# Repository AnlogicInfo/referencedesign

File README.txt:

Reference Design for Anlogic PLD devices.

Copyright 2011-2017 Anlogic Technologies.

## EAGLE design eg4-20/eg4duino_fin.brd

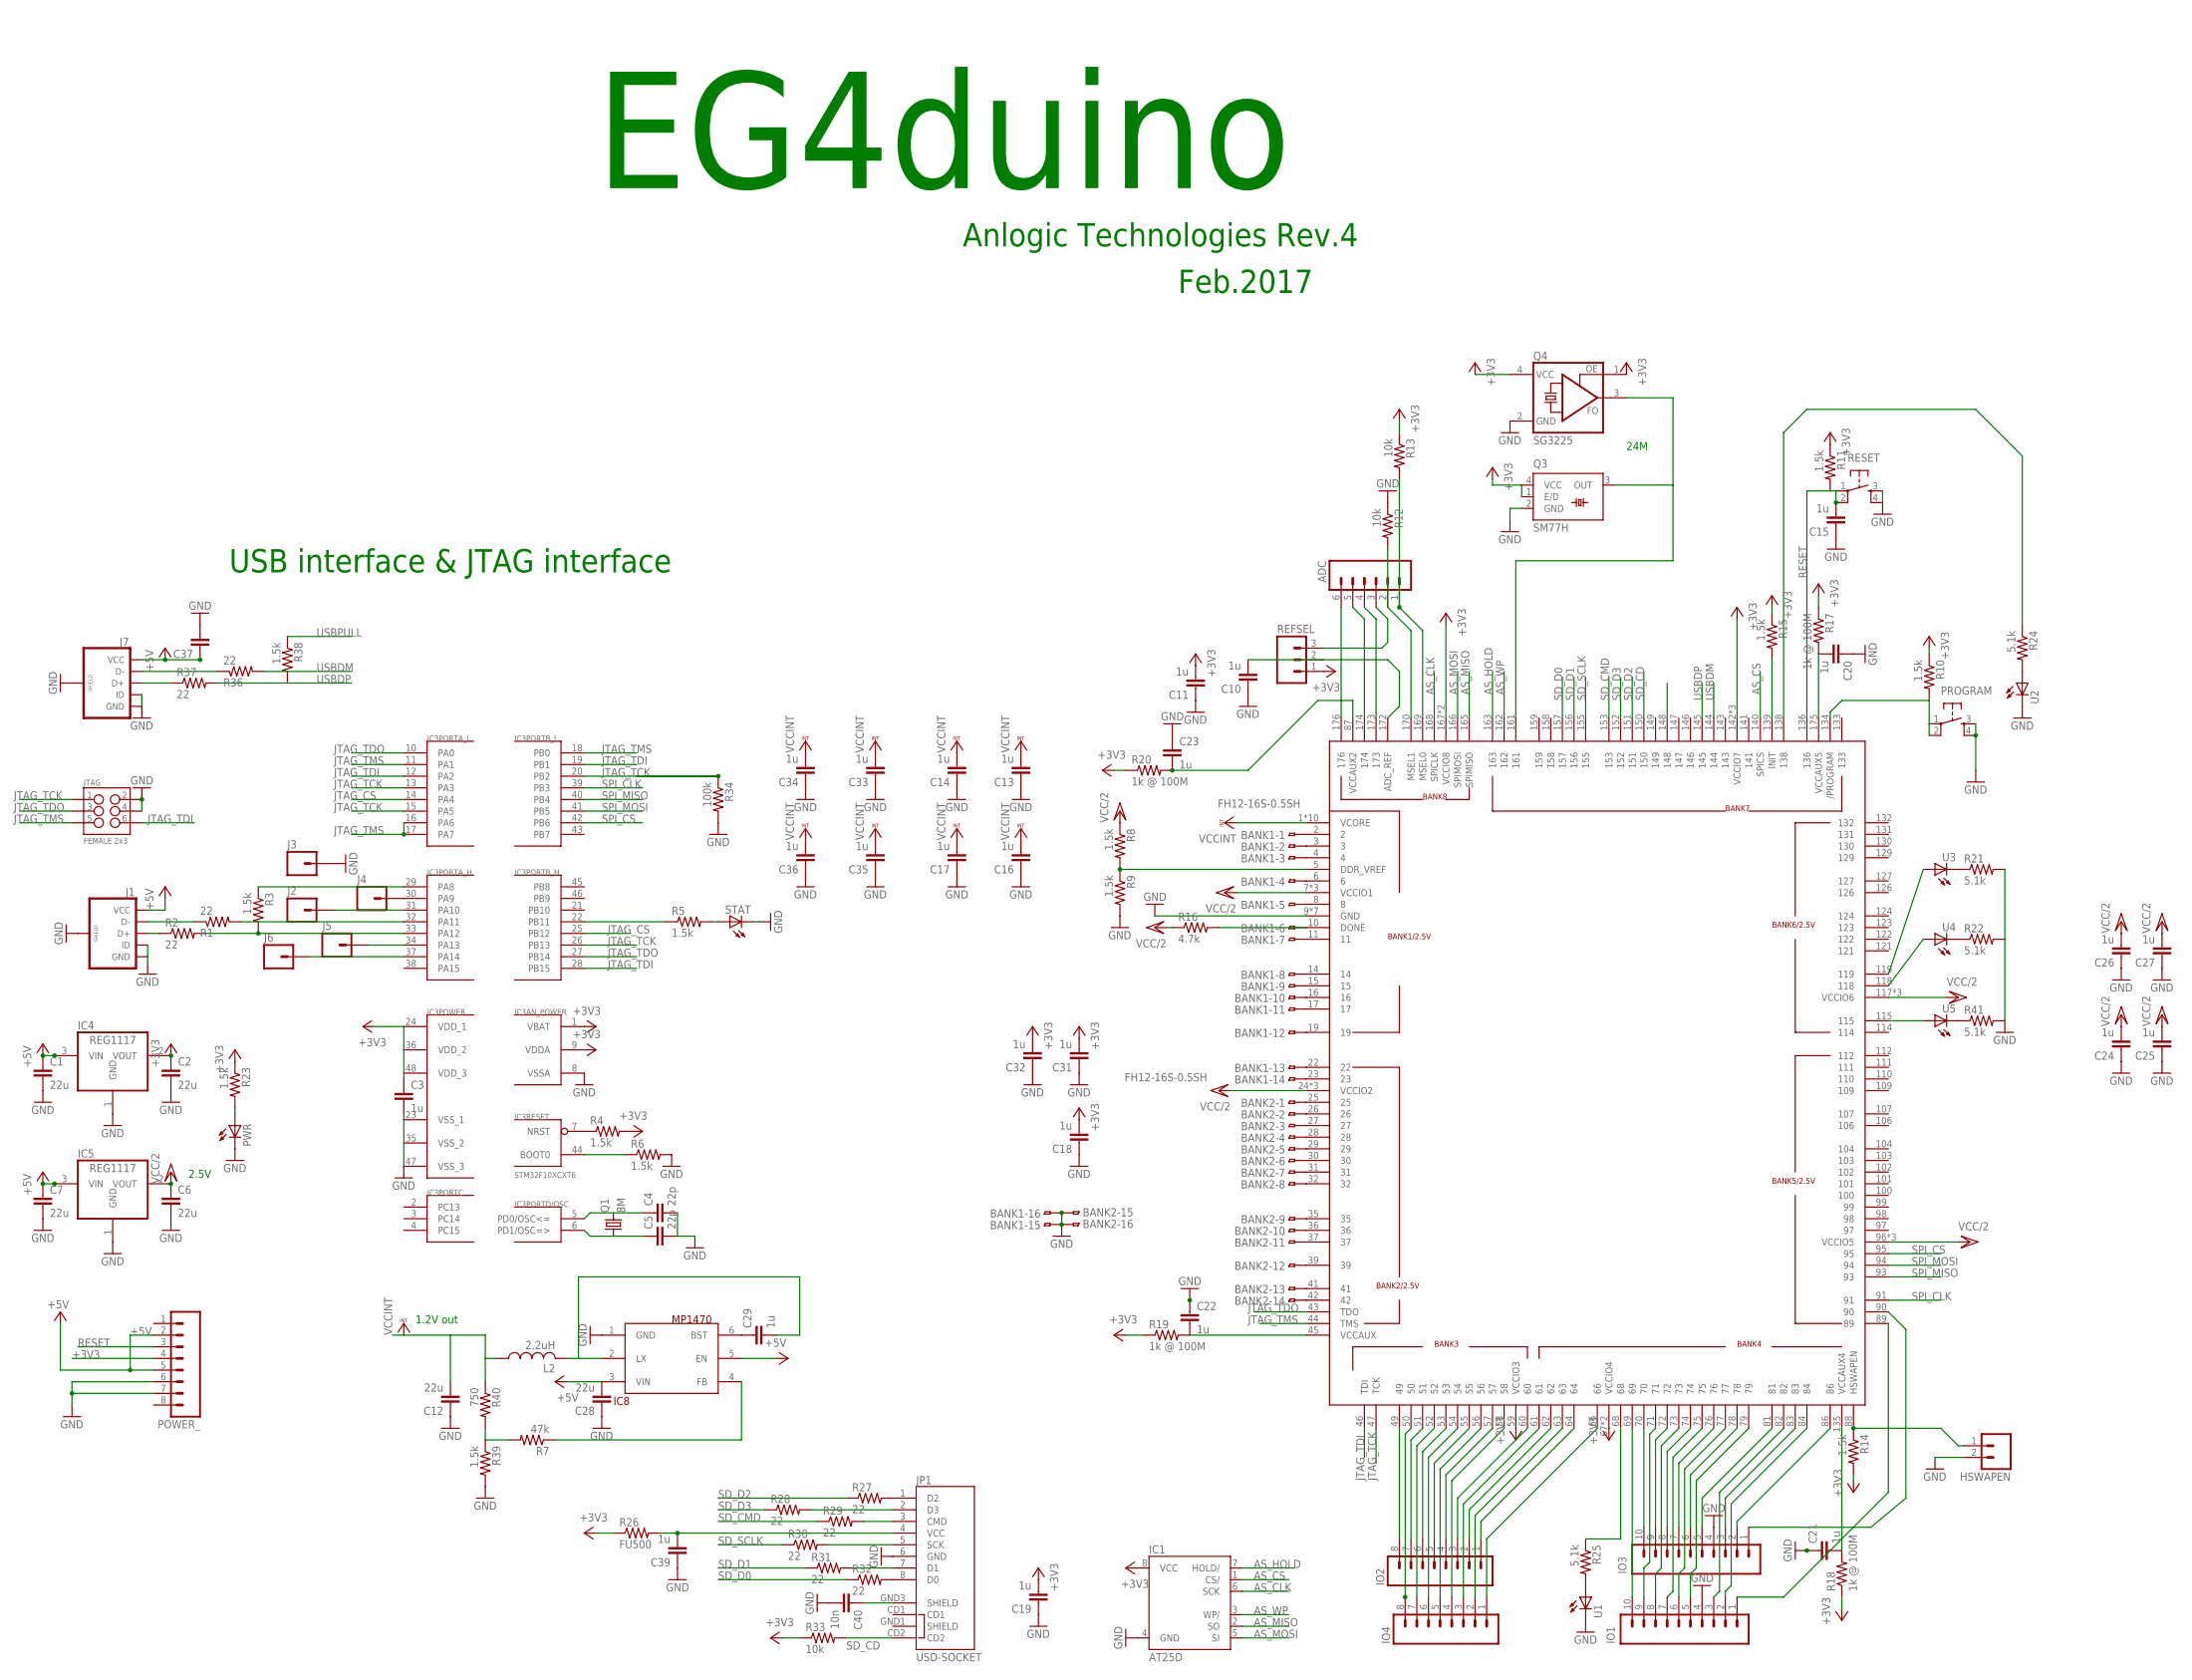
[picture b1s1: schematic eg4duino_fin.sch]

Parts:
ADC: M06SILK_FEMALE_PTH; 1X06
BANK1, BANK2: FH12-16S-0.5SH
C1, C2, C6, C7, C12, C28: 22u; C0805
C3, C10, C11, C13, C14, C15, C16, C17, C18, C19, C20, C21, C22, C23, C24, C25, C26, C27, C29, C31, C32, C33, C34, C35, C36, C39: 1u; C0805
C4, C5: 22p; C0805
C37: C-EUC0805; C0805
C40: 10n; C0805
HSWAPEN: M02PTH; 1X02
IC1: AT25D; SOIC8
IC2: EG4D20EG176; ELQFP176L
IC3: STM32F10XCXT6; TQFP48
IC4, IC5: REG1117; SOT223
IC8: MP1470; SOT23-6L
IO1, IO3: M10SILK_FEMALE_PTH; 1X10
IO2, IO4: M08SILK_FEMALE_PTH; 1X08
J1, J7: USB_MICROB_PLUGCONN-11752; USB-B-MICRO-SMD_V03
J2, J3, J4, J5, J6: M01; 0805SMD
JP1: USD-SOCKET; MICROSD_1:1
JTAG: FEMALE 2x3; 2X3
L2: 2.2uH; L4532P
POWER_: M08SILK_FEMALE_PTH; 1X08
PROGRAM: 10-XXSMD; B3F-10SMD
PWR: LEDCHIP-LED0805; CHIP-LED0805
Q1: 8M; HC49/S
Q3: SM77H
Q4: SG3225; 3225
R1, R2: 22; M0805
R3, R4, R5, R6, R23: 1.5k; M0805
R7: 47k; R0805
R8, R9, R11, R14, R15, R39: 1.5k; R0805
R10, R38: 1.5k; R0603
R12, R13, R33: 10k; R0805
R16: 4.7k; R0603
R17, R18, R19, R20: 1k @ 100M; R0805
R21, R22, R24, R25, R41: 5.1k; M0805
R26: FU500; R0805
R27, R28, R29, R30, R31, R32: 22; R0201
R34: 100k; R0603
R36, R37: 22; R0603W
R40: 750; R0805
REFSEL: M03PTH; 1X03
RESET: 10-XXSMD; B3F-10SMD
STAT: LEDCHIP-LED0805; CHIP-LED0805
U1, U2, U3, U4, U5: LEDCHIP-LED0805; CHIP-LED0805

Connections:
+3V3: C2.1, C3.1, C11.2, C18.2, C19.2, C31.2, C32.2, IC1.8 (VCC), IC2.59 (VCCIO3), IC2.67 (VCCIO4), IC2.80 (VCCIO4), IC2.142 (VCCIO7), IC2.154 (VCCIO7), IC2.160 (VCCIO7), IC2.167 (VCCIO8), IC2.171 (VCCIO8), IC3.1 (VBAT), IC3.9 (VDDA), IC3.24 (VDD_1), IC3.36 (VDD_2), IC3.48 (VDD_3), IC4.2 (VOUT), POWER_.4, Q3.1 (E/D), Q3.4 (VCC), Q4.1 (OE), Q4.4 (VCC), R4.2, R10.1, R11.1, R13.1, R14.2, R15.1, R17.1, R18.1, R19.1, R20.1, R23.1, R26.1, R33.1, REFSEL.1
+5V: C1.1, C7.1, C28.2, C37.1, IC4.3 (VIN), IC5.3 (VIN), IC8.3 (VIN), IC8.5 (EN), J1.VBUS (VCC), J7.VBUS (VCC), POWER_.2, POWER_.5
AS_CLK: IC1.6 (SCK), IC2.168 (SPICLK)
AS_CS: IC1.1 (CS/), IC2.140 (SPICS)
AS_HOLD: IC1.7 (HOLD/), IC2.163
AS_MISO: IC1.2 (SO), IC2.165 (SPIMISO)
AS_MOSI: IC1.5 (SI), IC2.166 (SPIMOSI)
AS_WP: IC1.3 (WP/), IC2.162
GND: BANK1.15, BANK1.16, BANK2.15, BANK2.16, C1.2, C2.2, C3.2, C4.2, C5.2, C6.2, C7.2, C10.1, C11.1, C12.1, C13.1, C14.1, C15.1, C16.1, C17.1, C18.1, C19.1, C20.1, C21.1, C22.1, C23.1, C24.1, C25.1, C26.1, C27.1, C28.1, C31.1, C32.1, C33.1, C34.1, C35.1, C36.1, C37.2, C39.1, C40.2, HSWAPEN.2, IC1.4 (GND), IC2.9 (GND), IC2.13 (GND), IC2.21 (GND), IC2.33 (GND), IC2.38 (GND), IC2.116 (GND), IC2.EGND (GND), IC3.8 (VSSA), IC3.23 (VSS_1), IC3.35 (VSS_2), IC3.47 (VSS_3), IC4.1 (GND), IC5.1 (GND), IC8.1 (GND), IO1.4, IO3.4, J1.GND, J1.ID, J1.SHIELD1 (SHIELD), J1.SHIELD2 (SHIELD), J1.SHIELD3 (SHIELD), J3.1, J7.GND, J7.ID, J7.SHIELD1 (SHIELD), J7.SHIELD2 (SHIELD), J7.SHIELD3 (SHIELD), JP1.6 (GND), JTAG.2, JTAG.4, POWER_.6, POWER_.7, PROGRAM.3 (S), PROGRAM.4 (S1), PWR.C, Q3.2 (GND), Q4.2 (GND), R6.2, R9.2, R12.1, R21.2, R22.2, R34.2, R39.2, R41.2, RESET.3 (S), RESET.4 (S1), STAT.C, U1.C, U2.C
JTAG_CS: IC3.14 (PA4), IC3.25 (PB12)
JTAG_TCK: IC2.47 (TCK), IC3.13 (PA3), IC3.15 (PA5), IC3.20 (PB2), IC3.26 (PB13), JTAG.1, R34.1
JTAG_TDI: IC2.46 (TDI), IC3.12 (PA2), IC3.19 (PB1), IC3.28 (PB15), JTAG.6
JTAG_TDO: IC2.43 (TDO), IC3.10 (PA0), IC3.27 (PB14), JTAG.3
JTAG_TMS: IC2.44 (TMS), IC3.11 (PA1), IC3.16 (PA6), IC3.17 (PA7), IC3.18 (PB0), JTAG.5
unnamed: ADC.6, IC2.176
unnamed: ADC.5, IC2.174
unnamed: ADC.4, IC2.173
unnamed: ADC.3, REFSEL.3
unnamed: ADC.2, IC2.170 (MSEL1), R12.2
unnamed: ADC.1, IC2.169 (MSEL0), R13.2
unnamed: IC2.69, IO1.10
unnamed: IC2.70, IO3.10
unnamed: IC2.71, IO1.9
unnamed: IC2.72, IO3.9
unnamed: IC2.73, IO1.8
unnamed: IC2.74, IO3.8
unnamed: IC2.75, IO1.7
unnamed: IC2.76, IO3.7
unnamed: IC2.77, IO1.6
unnamed: IC2.78, IO3.6
unnamed: IC2.79, IO1.5
unnamed: IC2.83, IO3.3
unnamed: IC2.81, IO3.5
unnamed: IC2.82, IO1.3
unnamed: IC2.84, IO1.2
unnamed: IC2.86, IO3.2
unnamed: IC2.89, IO1.1
unnamed: IC2.90, IO3.1
unnamed: J1.D+, R2.1
unnamed: J1.D-, R1.1
unnamed: IC3.32 (PA11), R1.2
unnamed: IC3.33 (PA12), R2.2, R3.2
unnamed: IC3.29 (PA8), R3.1
unnamed: IC3.31 (PA10), J2.1
unnamed: IC3.30 (PA9), J4.1
unnamed: IC3.7 (NRST), R4.1
unnamed: IC3.22 (PB11), R5.1
unnamed: R5.2, STAT.A
unnamed: C4.1, IC3.5 (PD0/OSC<=), Q1.2
unnamed: C5.1, IC3.6 (PD1/OSC=>), Q1.1
unnamed: IC3.44 (BOOT0), R6.1
unnamed: IC2.49, IO2.8
unnamed: IC2.51, IO2.7
unnamed: IC2.53, IO2.6
unnamed: IC2.54, IO4.6
unnamed: IC2.55, IO2.5
unnamed: IC2.56, IO4.5
unnamed: IC2.57, IO2.4
unnamed: IC2.58, IO4.4
unnamed: IC2.60, IO2.3
unnamed: IC2.61, IO4.3
unnamed: IC2.62, IO2.2
unnamed: IC2.63, IO4.2
unnamed: IC2.64, IO2.1
unnamed: IC2.66, IO4.1
unnamed: IC2.161, Q3.3 (OUT), Q4.3 (FO)
unnamed: C10.2, IC2.172 (ADC_REF), REFSEL.2
unnamed: IC2.119, U3.A
unnamed: IC2.118, U4.A
unnamed: C29.2, IC8.2 (LX), L2.2
unnamed: C29.1, IC8.6 (BST)
unnamed: IC8.4 (FB), R7.1
unnamed: R7.2, R39.1, R40.2
unnamed: IC2.5 (DDR_VREF), R8.2, R9.1
unnamed: BANK1.1, IC2.2
unnamed: BANK1.2, IC2.3
unnamed: BANK1.3, IC2.4
unnamed: BANK1.4, IC2.6
unnamed: BANK1.5, IC2.8
unnamed: IC3.34 (PA13), J5.1
unnamed: BANK1.7, IC2.11
unnamed: BANK1.8, IC2.14
unnamed: BANK1.9, IC2.15
unnamed: BANK1.10, IC2.16
unnamed: BANK1.11, IC2.17
unnamed: BANK1.12, IC2.19
unnamed: BANK1.13, IC2.22
unnamed: BANK1.14, IC2.23
unnamed: BANK2.1, IC2.25
unnamed: BANK2.2, IC2.26
unnamed: BANK2.3, IC2.27
unnamed: BANK2.4, IC2.28
unnamed: BANK2.5, IC2.29
unnamed: BANK2.6, IC2.30
unnamed: BANK2.7, IC2.31
unnamed: BANK2.8, IC2.32
unnamed: BANK2.9, IC2.35
unnamed: BANK2.10, IC2.36
unnamed: BANK2.11, IC2.37
unnamed: BANK2.12, IC2.39
unnamed: BANK2.13, IC2.41
unnamed: BANK2.14, IC2.42
unnamed: C20.2, IC2.175 (VCCAUX5), R17.2
unnamed: HSWAPEN.1, IC2.88 (HSWAPEN), R14.1
unnamed: IC2.139 (INIT), R15.2
unnamed: C21.2, IC2.135 (VCCAUX4), R18.2
unnamed: C22.2, IC2.45 (VCCAUX), R19.2
unnamed: C23.2, IC2.87 (VCCAUX2), R20.2
unnamed: IC2.115, U5.A
unnamed: PWR.A, R23.2
unnamed: R24.2, U2.A
unnamed: IC2.138, R24.1
unnamed: R25.2, U1.A
unnamed: IC2.68, R25.1
unnamed: C39.2, JP1.4 (VCC), R26.2
unnamed: JP1.1 (D2), R27.2
unnamed: IC2.134 (/PROGRAM), PROGRAM.1, PROGRAM.2 (P1), R10.2
unnamed: JP1.2 (D3), R28.2
unnamed: JP1.3 (CMD), R29.2
unnamed: JP1.8 (D0), R32.2
unnamed: JP1.7 (D1), R31.2
unnamed: IC3.37 (PA14), J6.1
unnamed: JP1.5 (SCK), R30.2
unnamed: C40.1, JP1.GND3 (SHIELD)
unnamed: BANK1.6, IC2.10 (DONE), R16.2
unnamed: J7.D-, R36.1
unnamed: J7.D+, R37.1
unnamed: R21.1, U3.C
unnamed: R22.1, U4.C
unnamed: R41.1, U5.C
RESET: C15.2, IC2.136, POWER_.3, R11.2, RESET.1, RESET.2 (P1)
SD_CD: IC2.150, JP1.CD2, R33.2
SD_CMD: IC2.153, R29.1
SD_D0: IC2.157, R32.1
SD_D1: IC2.156, R31.1
SD_D2: IC2.151, R27.1
SD_D3: IC2.152, R28.1
SD_SCLK: IC2.155, R30.1
SPI_CLK: IC2.91, IC3.39 (PB3)
SPI_CS: IC2.95, IC3.42 (PB6)
SPI_MISO: IC2.93, IC3.40 (PB4)
SPI_MOSI: IC2.94, IC3.41 (PB5)
USBDM: IC2.144, R36.2
USBDP: IC2.145, R37.2, R38.2
USBPULL: IC2.148, R38.1
USER_RX: IC2.52, IO4.7
USER_TX: IC2.50, IO4.8
VCC/2: C6.1, C24.2, C25.2, C26.2, C27.2, IC2.7 (VCCIO1), IC2.12 (VCCIO1), IC2.18 (VCCIO1), IC2.24 (VCCIO2), IC2.34 (VCCIO2), IC2.40 (VCCIO2), IC2.96 (VCCIO5), IC2.105 (VCCIO5), IC2.108 (VCCIO5), IC2.117 (VCCIO6), IC2.120 (VCCIO6), IC2.125 (VCCIO6), IC5.2 (VOUT), R8.1, R16.1
VCCINT: C12.2, C13.2, C14.2, C16.2, C17.2, C33.2, C34.2, C35.2, C36.2, IC2.1 (VCORE), IC2.20 (VCORE), IC2.48 (VCORE), IC2.65 (VCORE), IC2.85 (VCORE), IC2.92 (VCORE), IC2.113 (VCORE), IC2.128 (VCORE), IC2.137 (VCORE), IC2.164 (VCORE), L2.1, R40.1

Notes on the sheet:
1.2V out
2.5V
EG4duino
Anlogic Technologies Rev.4
Feb.2017
USB interface & JTAG interface
24M

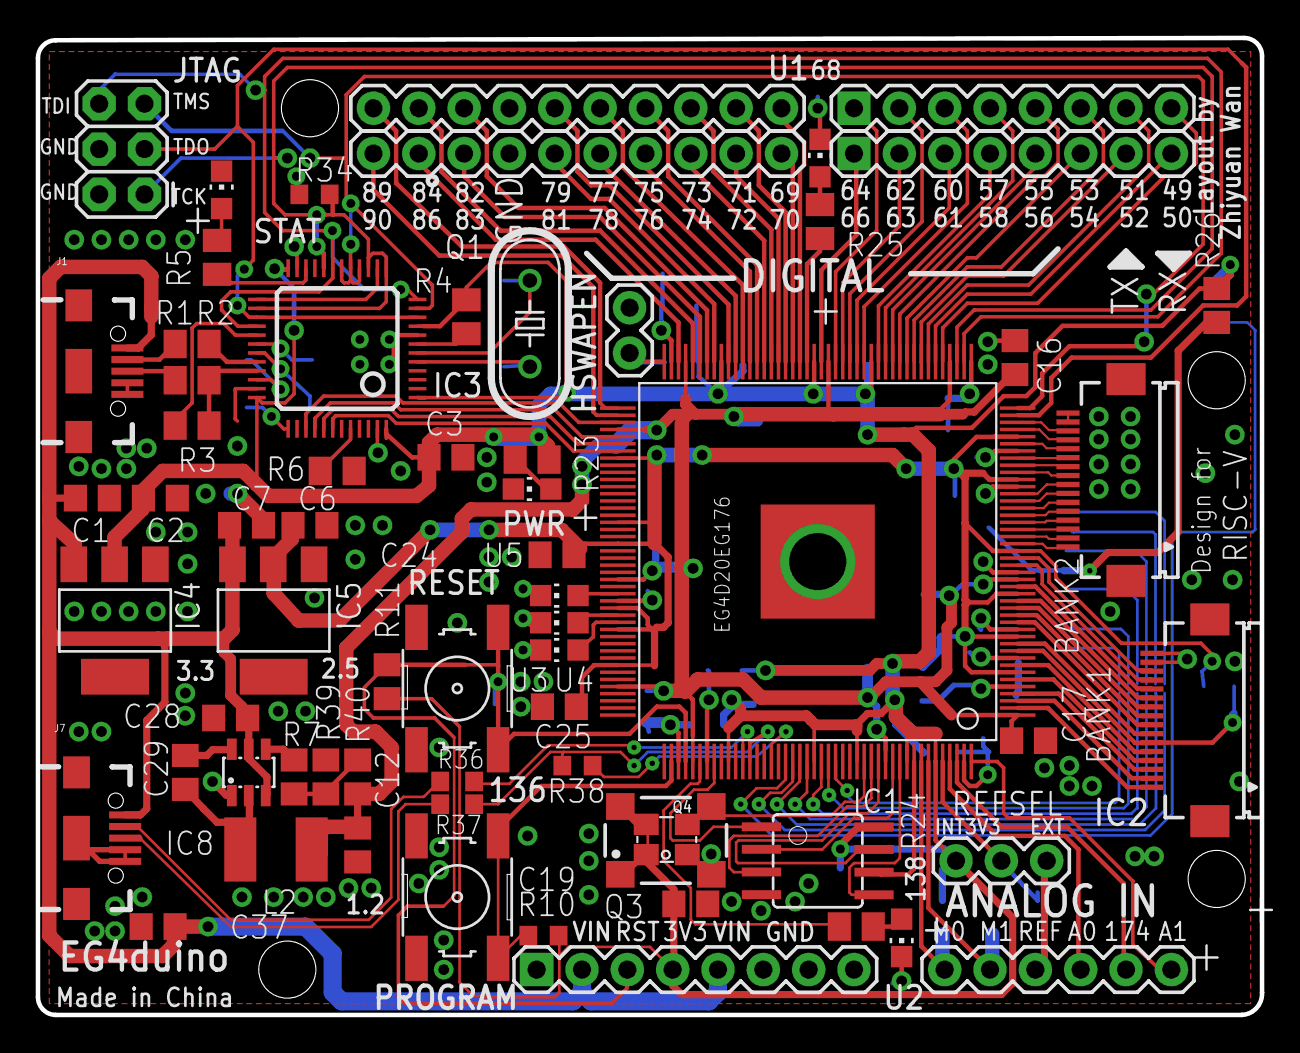
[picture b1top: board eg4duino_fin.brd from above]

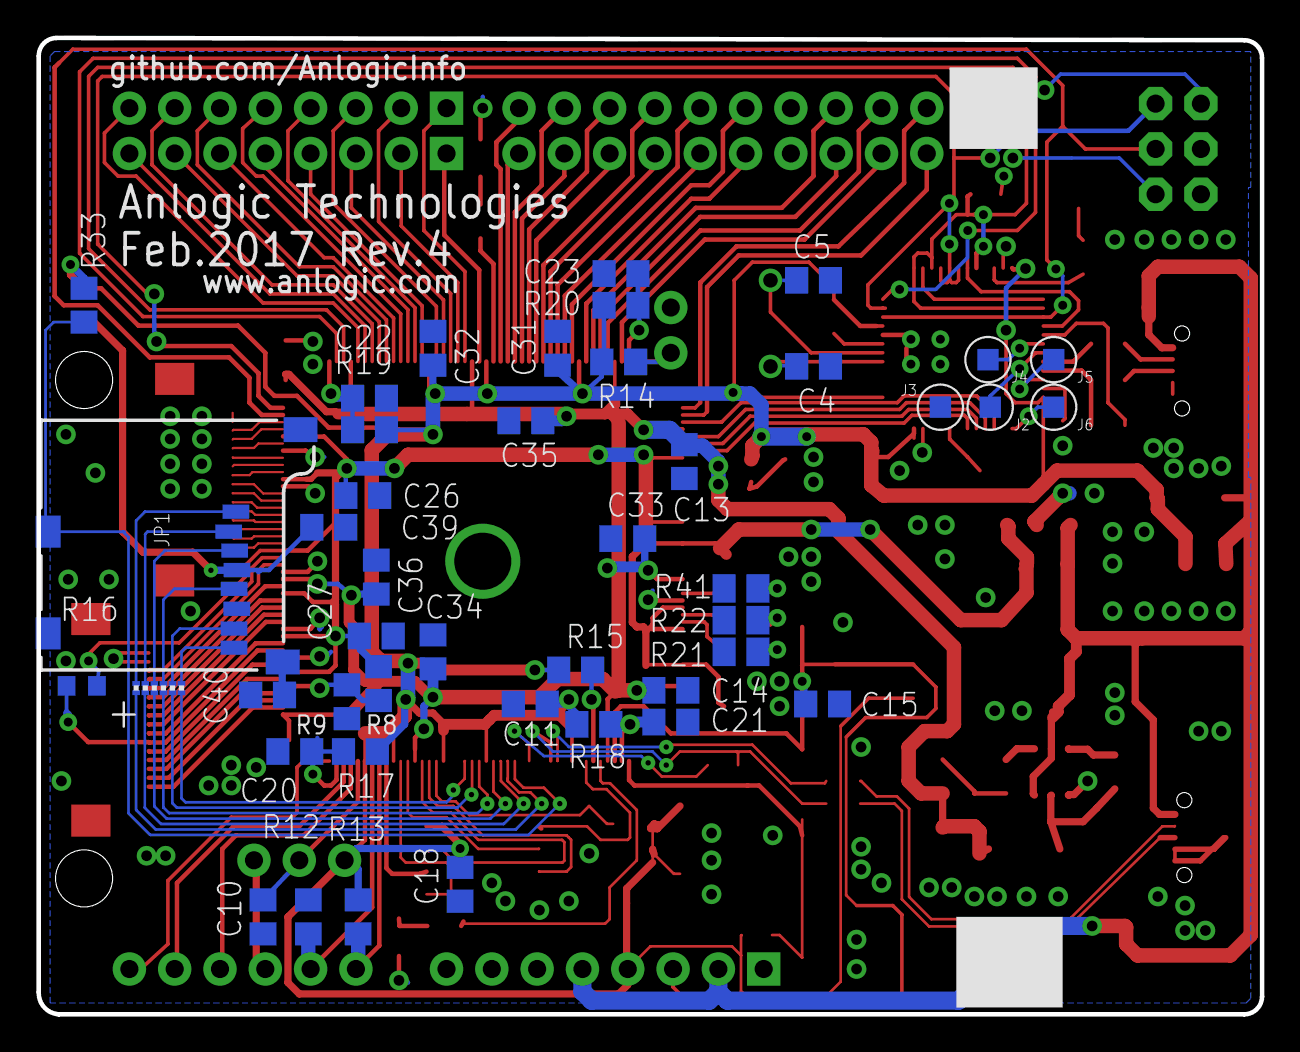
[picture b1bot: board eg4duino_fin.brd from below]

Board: 2 copper layers, 68.6 x 54.7 mm, 114 parts (49 on the bottom side), 149 nets.

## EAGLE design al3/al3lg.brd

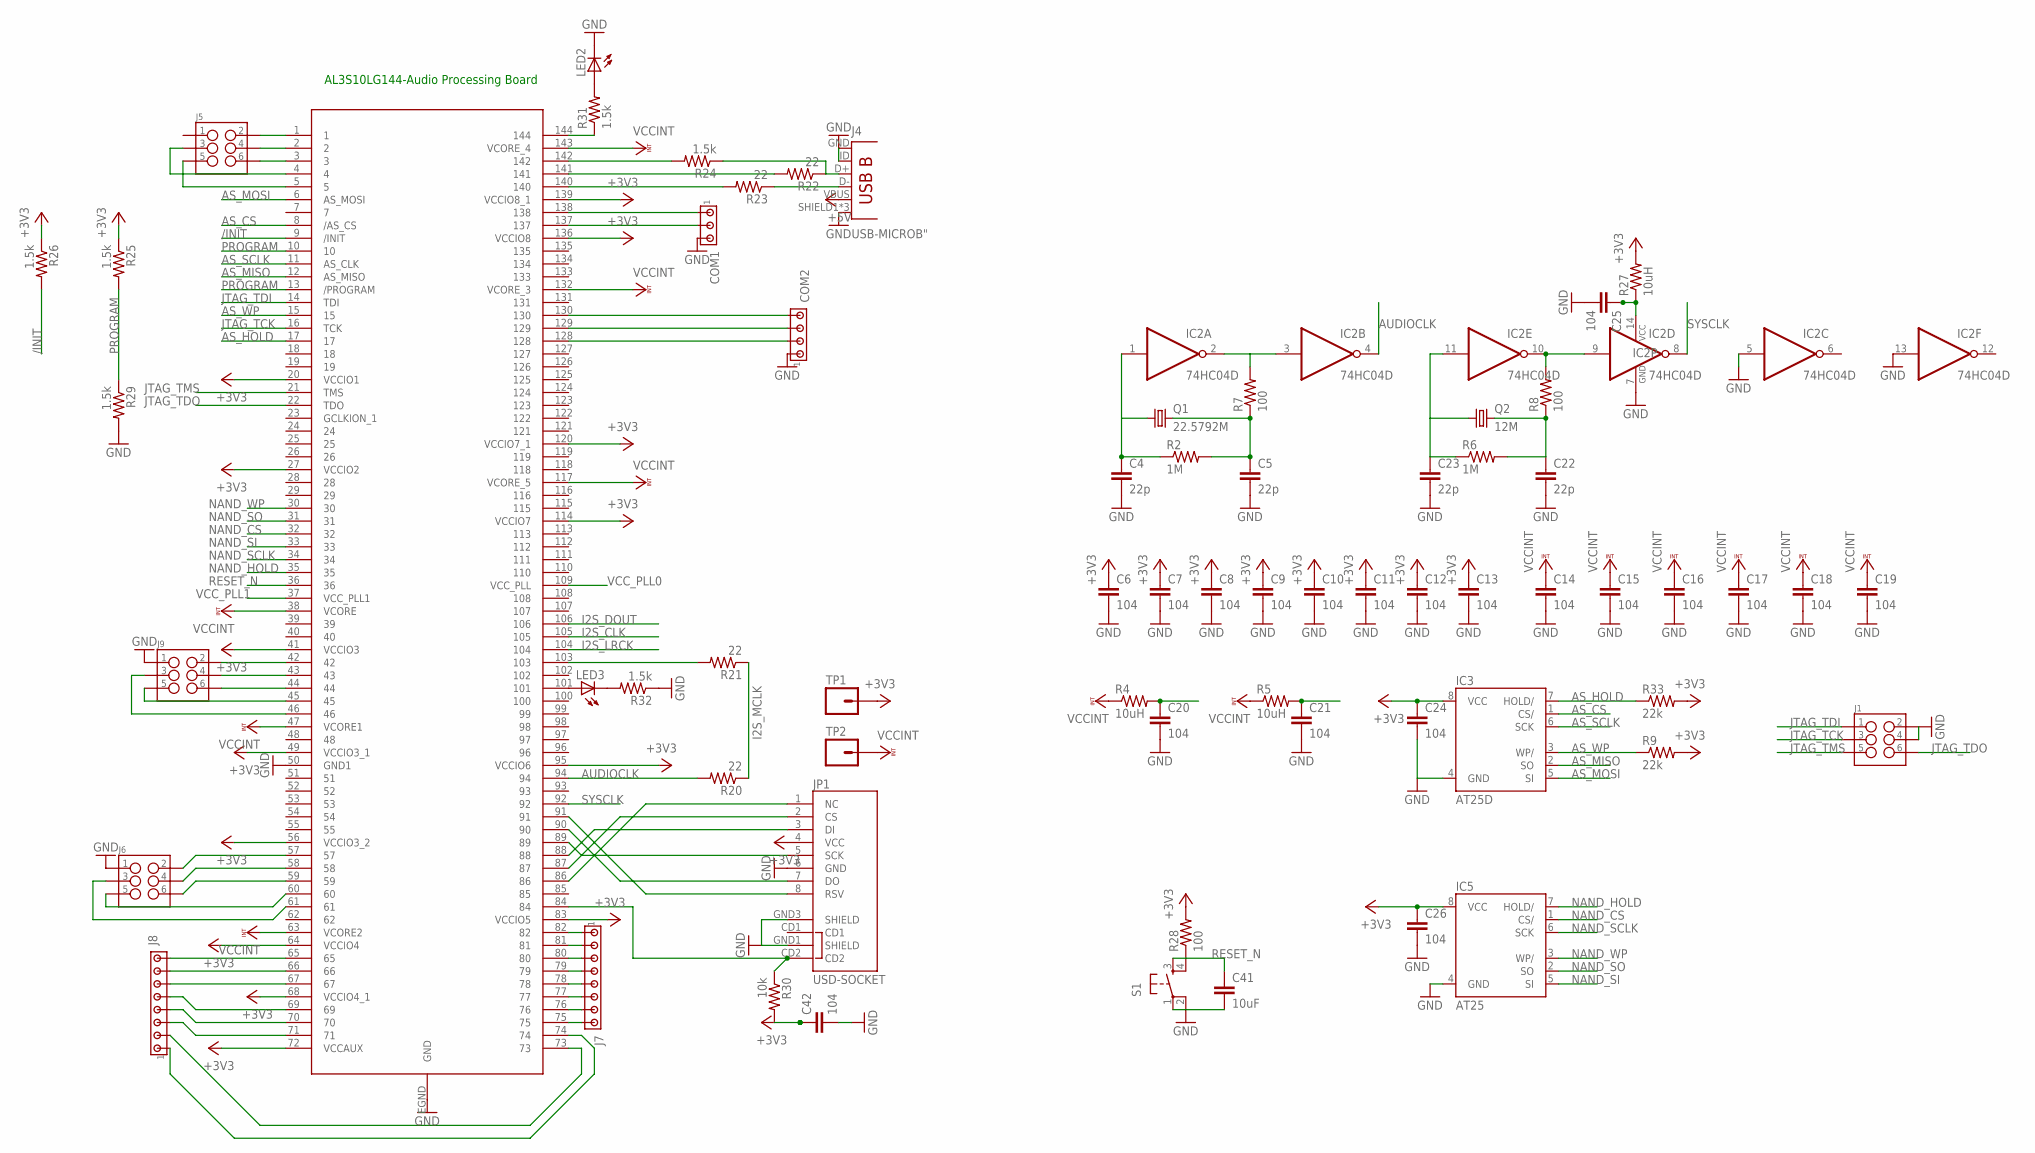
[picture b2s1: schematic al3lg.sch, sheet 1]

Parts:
C4, C5, C22, C23: 22p; C0805
C6, C7, C8, C9, C10, C11, C12, C13, C14, C15, C16, C17, C18, C19, C20, C21, C24, C25, C26, C42: 104; C0805
C41: 10uF; C0805
COM1: MTA03-100; 10X03MTA
COM2: MTA04-100; 10X04MTA
IC2: 74HC04D; SO14
IC3: AT25D; SOIC8
IC5: AT25; WSON8
J1, J5, J6, J9: M03X22X3_SILK_MALE_PTH; 2X3
J4: USB-MICROB"; USB-B-MICRO-SMD_V03
J7, J8: MTA08-100; 10X08MTA
JP1: USD-SOCKET; MICROSD_1:1
LED2, LED3: LEDSML0805; SML0805
Q1: 22.5792M; HC49/S
Q2: 12M; HC49/S
R2, R6: 1M; M0805
R4, R5, R27: 10uH; M0805
R7, R8, R28: 100; M0805
R9, R33: 22k; M0805
R20, R21, R22, R23: 22; M0805
R24, R25, R26, R29: 1.5k; M0805
R30: 10k; M0805
R31, R32: 1.5k; R0805
S1: 10-XXSMD; B3F-10SMD
TP1, TP2: M01; 0805SMD
U1: AL3S10LG144; HLQFP144NT16

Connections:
+3V3: C6.1, C7.1, C8.1, C9.1, C10.1, C11.1, C12.1, C13.1, C24.1, C26.1, C42.1, IC3.8 (VCC), IC5.8 (VCC), JP1.4 (VCC), R9.2, R25.1, R26.1, R27.2, R28.2, R30.2, R33.2, TP1.1, U1.20 (VCCIO1), U1.27 (VCCIO2), U1.41 (VCCIO3), U1.49 (VCCIO3_1), U1.56 (VCCIO3_2), U1.64 (VCCIO4), U1.68 (VCCIO4_1), U1.72 (VCCAUX), U1.83 (VCCIO5), U1.95 (VCCIO6), U1.114 (VCCIO7), U1.120 (VCCIO7_1), U1.136 (VCCIO8), U1.139 (VCCIO8_1); also elsewhere on the board
+5V: J4.VBUS; also elsewhere on the board
/INIT: R26.2, U1.9 (/INIT)
AS_CS: IC3.1 (CS/), U1.8 (/AS_CS)
AS_HOLD: IC3.7 (HOLD/), R33.1, U1.17
AS_MISO: IC3.2 (SO), U1.12 (AS_MISO)
AS_MOSI: IC3.5 (SI), U1.6 (AS_MOSI)
AS_SCLK: IC3.6 (SCK), U1.11 (AS_CLK)
AS_WP: IC3.3 (WP/), R9.1, U1.15
AUDIOCLK: IC2.4 (O), R20.2, U1.94
DI: J6.4, U1.58
DI1: J9.4, U1.43
DO: J6.2, U1.57
DO1: J9.2, U1.42
GND: C4.2, C5.2, C6.2, C7.2, C8.2, C9.2, C10.2, C11.2, C12.2, C13.2, C14.2, C15.2, C16.2, C17.2, C18.2, C19.2, C20.2, C21.2, C22.2, C23.2, C24.2, C25.2, C26.2, C41.2, C42.2, COM1.3, COM2.1, IC2.5 (I), IC2.7 (GND), IC2.13 (I), IC3.4 (GND), IC5.4 (GND), J1.2, J1.4, J4.GND, J4.ID (USBID), J4.SHIELD1 (SHIELD), J4.SHIELD2 (SHIELD), J4.SHIELD3 (SHIELD), J6.1, J9.1, JP1.6 (GND), JP1.GND1 (SHIELD), JP1.GND3 (SHIELD), LED2.C, R29.2, R32.1, S1.1, S1.2 (P1), U1.50 (GND1), U1.EGND (GND); also elsewhere on the board
I2S_CLK: U1.105; also elsewhere on the board
I2S_DOUT: U1.106; also elsewhere on the board
I2S_LRCK: U1.104; also elsewhere on the board
I2S_MCLK: R20.1, R21.1; also elsewhere on the board
JTAG_TCK: J1.3, U1.16 (TCK)
JTAG_TDI: J1.1, U1.14 (TDI)
JTAG_TDO: J1.6, U1.22 (TDO)
JTAG_TMS: J1.5, U1.21 (TMS)
LRCLK: J6.6, U1.59
LRCLK1: J9.6, U1.44
MCLK: J6.5, U1.60
MCLK1: J9.5, U1.45
unnamed: C4.1, IC2.1 (I), Q1.1, R2.1
unnamed: C5.1, Q1.2, R2.2, R7.1
unnamed: C23.1, IC2.11 (I), Q2.1, R6.1
unnamed: IC2.2 (O), IC2.3 (I), R7.2
unnamed: C22.1, Q2.2, R6.2, R8.1
unnamed: IC2.9 (I), IC2.10 (O), R8.2
unnamed: R21.2, U1.103
unnamed: R24.2, U1.142
unnamed: J4.D+, R22.1, R24.1
unnamed: R22.2, U1.141
unnamed: R23.2, U1.140
unnamed: J4.D-, R23.1
unnamed: COM1.1, U1.138
unnamed: COM1.2, U1.137
unnamed: C25.1, IC2.14 (VCC), R27.1
unnamed: J8.8, U1.65
unnamed: J8.7, U1.66
unnamed: J8.6, U1.67
unnamed: J8.2, U1.73
unnamed: J8.5, U1.69
unnamed: J8.4, U1.70
unnamed: J8.3, U1.71
unnamed: J8.1, U1.74
unnamed: J7.1, U1.82
unnamed: J7.2, U1.81
unnamed: J7.3, U1.80
unnamed: J7.4, U1.79
unnamed: J7.5, U1.78
unnamed: J7.6, U1.77
unnamed: J7.7, U1.76
unnamed: JP1.CD2, R30.1, U1.84
unnamed: JP1.8 (RSV), U1.91
unnamed: JP1.7 (DO), U1.90
unnamed: JP1.5 (SCK), U1.89
unnamed: JP1.3 (DI), U1.88
unnamed: JP1.2 (CS), U1.87
unnamed: JP1.1 (NC), U1.86
unnamed: COM2.4, U1.130
unnamed: COM2.3, U1.129
unnamed: COM2.2, U1.128
unnamed: LED2.A, R31.2
unnamed: R31.1, U1.144
unnamed: J5.2, U1.1
unnamed: J5.4, U1.2
unnamed: J5.6, U1.3
unnamed: J5.3, U1.4
unnamed: J5.5, U1.5
unnamed: LED3.A, U1.101
unnamed: LED3.C, R32.2
unnamed: J7.8, U1.75
NAND_CS: IC5.1 (CS/), U1.32
NAND_HOLD: IC5.7 (HOLD/), U1.35
NAND_SCLK: IC5.6 (SCK), U1.34
NAND_SI: IC5.5 (SI), U1.33
NAND_SO: IC5.2 (SO), U1.31
NAND_WP: IC5.3 (WP/), U1.30
PROGRAM: R25.2, R29.1, U1.10, U1.13 (/PROGRAM)
RESET_N: C41.1, R28.1, S1.3 (S), S1.4 (S1), U1.36
SCLK: J6.3, U1.61
SCLK1: J9.3, U1.46
SYSCLK: IC2.8 (O), U1.92
VCCINT: C14.1, C15.1, C16.1, C17.1, C18.1, C19.1, R4.1, R5.1, TP2.1, U1.38 (VCORE), U1.47 (VCORE1), U1.63 (VCORE2), U1.117 (VCORE_5), U1.132 (VCORE_3), U1.143 (VCORE_4); also elsewhere on the board
VCC_PLL0: C21.1, R5.2, U1.109 (VCC_PLL)
VCC_PLL1: C20.1, R4.2, U1.37 (VCC_PLL1)

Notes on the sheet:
AL3S10LG144-Audio Processing Board

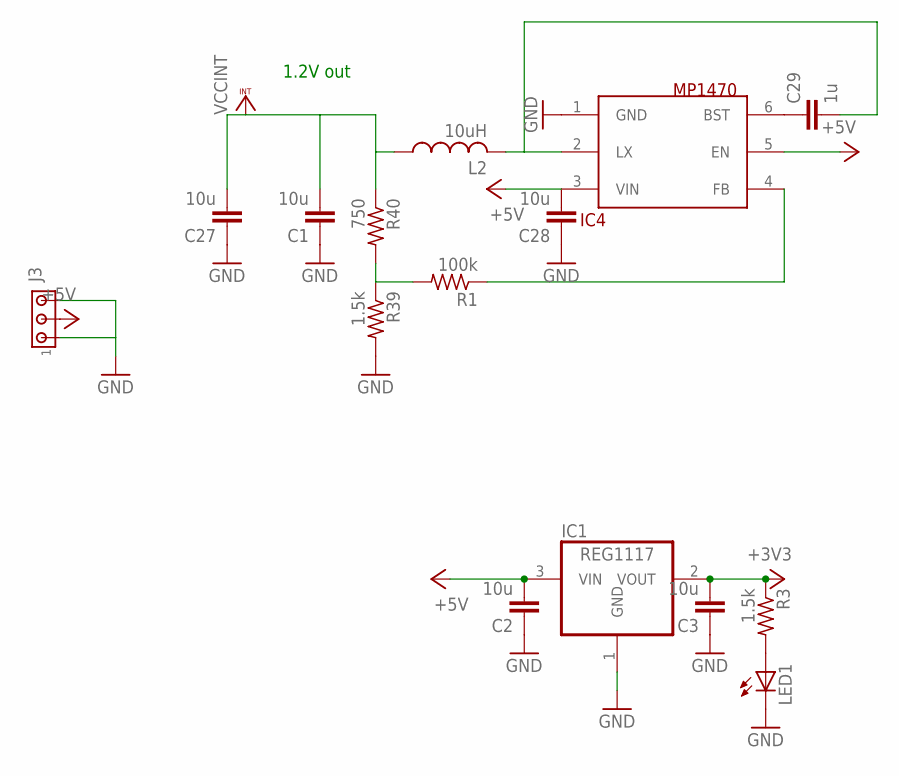
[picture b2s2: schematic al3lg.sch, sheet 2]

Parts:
C1, C2, C3, C27, C28: 10u; C0805
C29: 1u; C0805
IC1: REG1117; SOT223
IC4: MP1470; SOT23-6L
J3: MTA03-100; 10X03MTA
L2: 10uH; L4532P
LED1: LEDSML0805; SML0805
R1: 100k; R0805
R3, R39: 1.5k; R0805
R40: 750; R0805

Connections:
+3V3: C3.2, IC1.2 (VOUT), R3.1; also elsewhere on the board
+5V: C2.2, C28.2, IC1.3 (VIN), IC4.3 (VIN), IC4.5 (EN), J3.2; also elsewhere on the board
GND: C1.1, C2.1, C3.1, C27.1, C28.1, IC1.1 (GND), IC4.1 (GND), J3.1, J3.3, LED1.C, R39.2; also elsewhere on the board
unnamed: R1.2, R39.1, R40.2
unnamed: LED1.A, R3.2
unnamed: C29.2, IC4.2 (LX), L2.2
unnamed: C29.1, IC4.6 (BST)
unnamed: IC4.4 (FB), R1.1
VCCINT: C1.2, C27.2, L2.1, R40.1; also elsewhere on the board

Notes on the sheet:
1.2V out

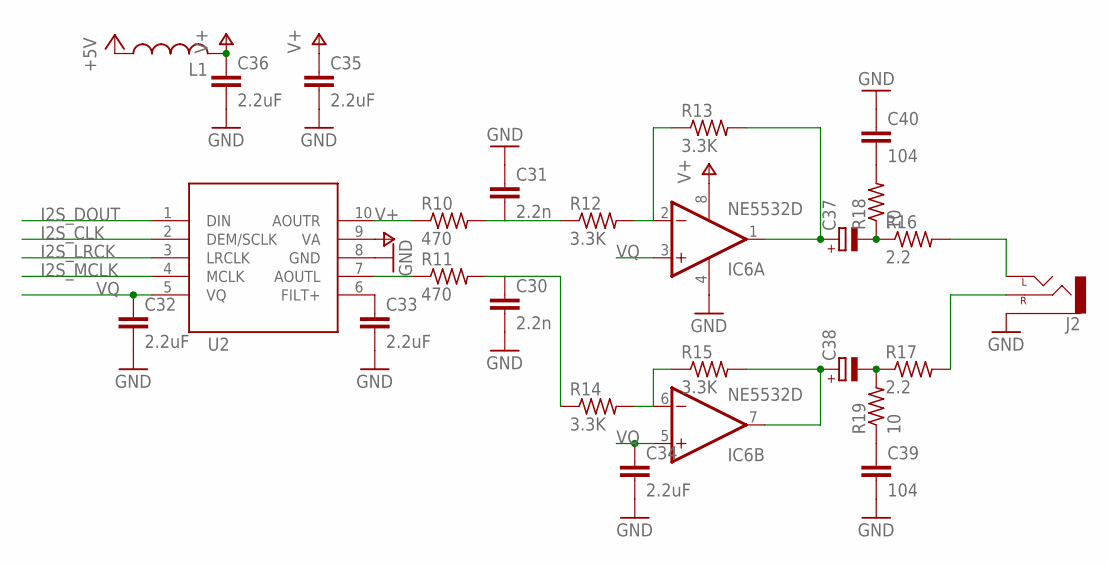
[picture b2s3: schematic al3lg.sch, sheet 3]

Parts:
C30, C31: 2.2n; C0805
C32, C33, C34, C35, C36: 2.2uF; C0805
C37, C38: CPOL-EUE2.5-7; E2,5-7
C39, C40: 104; C0805
IC6: NE5532D; SO08
J2: AUDIO-JACKPTH; AUDIO-JACK
L1: L-USL4532P; L4532P
R10, R11: 470; R0805
R12, R13, R14, R15: 3.3K; R0805
R16, R17: 2.2; R0805
R18, R19: 10; R0805
U2: CS4344; TSSOP10

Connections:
+5V: L1.1; also elsewhere on the board
GND: C30.2, C31.1, C32.2, C33.2, C34.2, C35.2, C36.2, C39.2, C40.1, IC6.4 (V-), J2.SLEEVE, U2.8 (GND); also elsewhere on the board
I2S_CLK: U2.2 (DEM/SCLK); also elsewhere on the board
I2S_DOUT: U2.1 (DIN); also elsewhere on the board
I2S_LRCK: U2.3 (LRCLK); also elsewhere on the board
I2S_MCLK: U2.4 (MCLK); also elsewhere on the board
unnamed: R11.1, U2.7 (AOUTL)
unnamed: C30.1, R11.2, R14.1
unnamed: R10.1, U2.10 (AOUTR)
unnamed: C31.2, R10.2, R12.1
unnamed: IC6.2 (-IN), R12.2, R13.1
unnamed: C37.+, IC6.1 (OUT), R13.2
unnamed: IC6.6 (-IN), R14.2, R15.1
unnamed: C38.+, IC6.7 (OUT), R15.2
unnamed: C33.1, U2.6 (FILT+)
unnamed: C37.-, R16.1, R18.1
unnamed: C38.-, R17.1, R19.2
unnamed: J2.TIP (LEFT), R16.2
unnamed: J2.RING (RIGHT), R17.2
unnamed: C39.1, R19.1
unnamed: C40.2, R18.2
V+: C35.1, C36.1, IC6.8 (V+), L1.2, U2.9 (VA)
VQ: C32.1, C34.1, IC6.3 (+IN), IC6.5 (+IN), U2.5 (VQ)

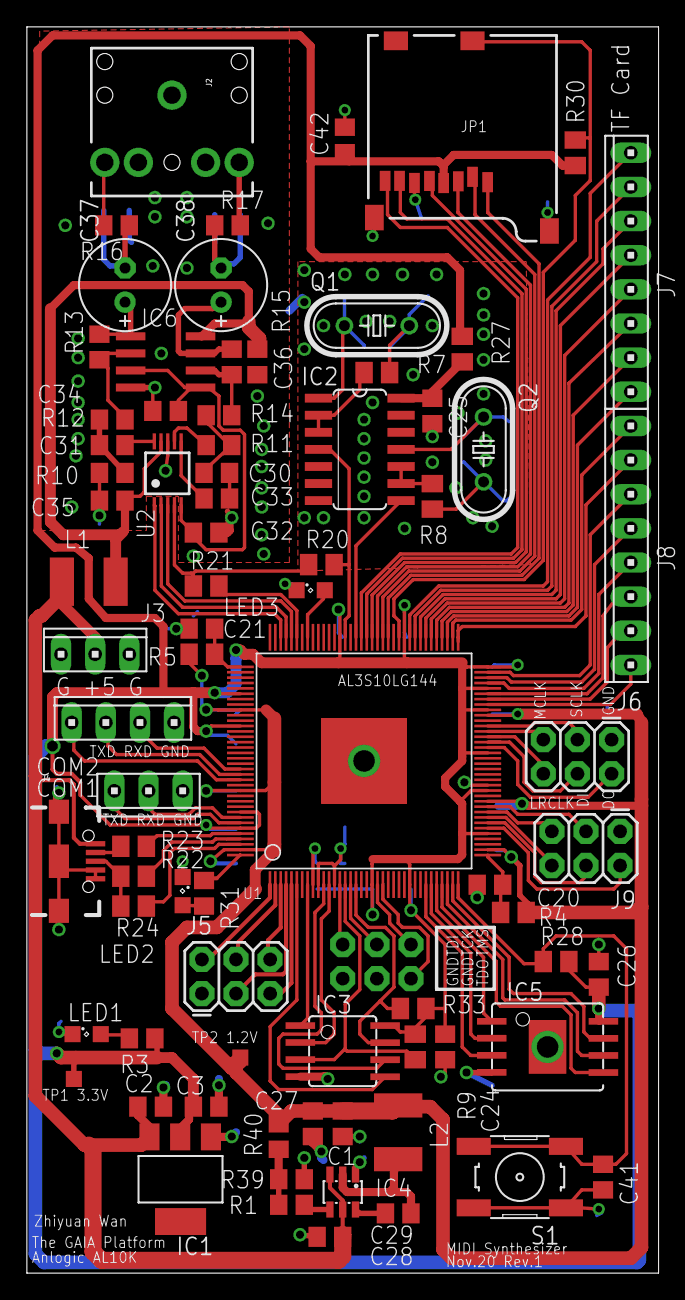
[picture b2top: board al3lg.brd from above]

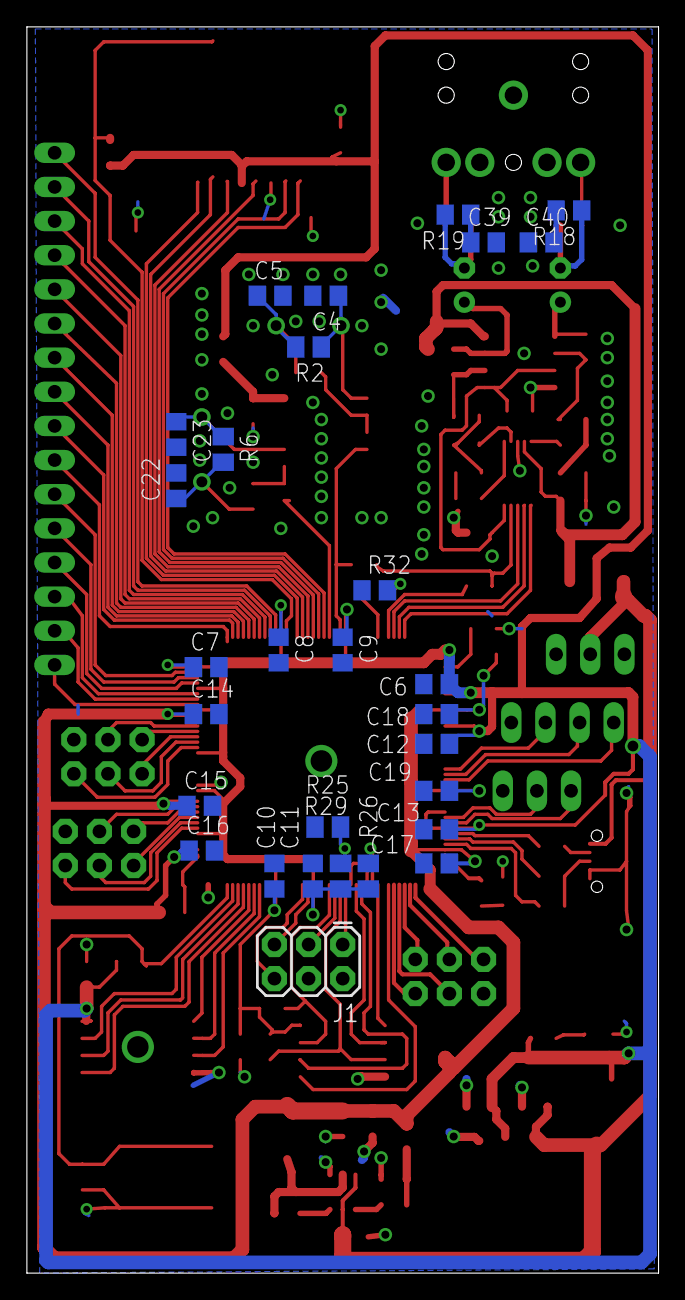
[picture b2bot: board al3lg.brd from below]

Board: 2 copper layers, 47.0 x 92.7 mm, 107 parts (29 on the bottom side), 113 nets.

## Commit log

2018-01-02 Import AL3, EG4-20 design

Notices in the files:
parts and their libraries:
SparkFun-Connectors: Licensing: Creative Commons ShareAlike 4.0 International - https://creativecommons.org/licenses/by-sa/4.0
